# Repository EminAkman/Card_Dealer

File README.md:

# CDM (Kart Dağıtıcı Makine)

Bu repo, hem kendimi geliştirmek hem de geliştirme ve kullanım sürecinde keyif almak amacıyla tasarladığım otomatik kart dağıtma makinesinin (Card Dealing Machine - CDM) tasarım, yazılım ve donanım dosyalarını içerir.

## Proje Yapısı

- **[CAD_Files](CAD_Files/)**: Mekanik gövde ve parçalara ait 3B CAD tasarımları ve montaj dosyaları.
  - **[Upper_Parts](CAD_Files/Upper_Parts/)**: Kart haznesi, karıştırma ve itme mekanizması parçaları.
  - **[Middle_Parts](CAD_Files/Middle_Parts/)**: Kart fırlatma mekanizması ve OLED ekran montaj parçaları.
  - **[Lower_Parts](CAD_Files/Lower_Parts/)**: Taban gövdesi, motorlar, sensörler ve elektronik taşıyıcı parçaları.
- **[Code](Code/)**: Makinenin gömülü yazılımı ve kaynak kodları.
- **[PCB_Files](PCB_Files/)**: Elektronik devre kartı (PCB) tasarımları ve şematikler.

## Lisans

Bu proje [GPL-3.0](LICENSE) kapsamında lisanslanmıştır.

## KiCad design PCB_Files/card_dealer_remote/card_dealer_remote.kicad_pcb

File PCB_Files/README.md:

# PCB ve Elektronik Tasarımlar

Bu dizin, Kart Dağıtıcı Makine'nin (CDM) elektronik devre şemalarını, baskı devre kartı (PCB) tasarımlarını ve elektronik bileşen CAD modellerini içerir.

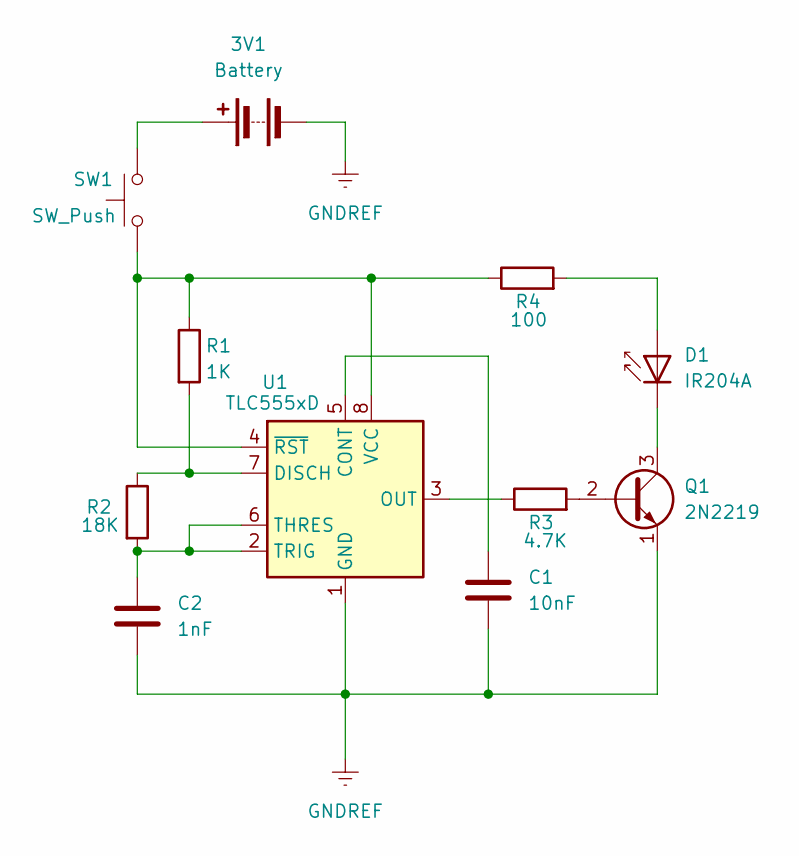
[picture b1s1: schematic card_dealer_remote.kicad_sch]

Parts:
3V1: Battery; BatteryHolder_MYOUNG_BS-07-A1BJ001_CR2032
C1: 10nF; CP_Radial_D5.0mm_P2.00mm
C2: 1nF; CP_Radial_D5.0mm_P2.00mm
D1: IR204A; LED_D3.0mm_IRBlack
Q1: 2N2219; TO-39-3
R1: 1K; R_Axial_DIN0207_L6.3mm_D2.5mm_P7.62mm_Horizontal
R2: 18K; R_Axial_DIN0207_L6.3mm_D2.5mm_P7.62mm_Horizontal
R3: 4.7K; R_Axial_DIN0207_L6.3mm_D2.5mm_P7.62mm_Horizontal
R4: 100; R_Axial_DIN0207_L6.3mm_D2.5mm_P7.62mm_Horizontal
SW1: SW_Push; SW_PUSH-12mm
U1: TLC555xD; DIP-8_W7.62mm

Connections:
GNDREF: 3V1.2 (-), C1.2, C2.2, Q1.1 (E), U1.1 (GND)
unnamed: 3V1.1 (+), SW1.2
unnamed: D1.2 (A), R4.2
unnamed: D1.1 (K), Q1.3 (C)
unnamed: Q1.2 (B), R3.2
unnamed: C1.1, U1.5 (CONT)
unnamed: R1.2, R2.1, U1.7 (DISCH)
unnamed: R3.1, U1.3 (OUT)
unnamed: C2.1, R2.2, U1.2 (TRIG), U1.6 (THRES)
unnamed: R1.1, R4.1, SW1.1, U1.4 (~RST), U1.8 (VCC)

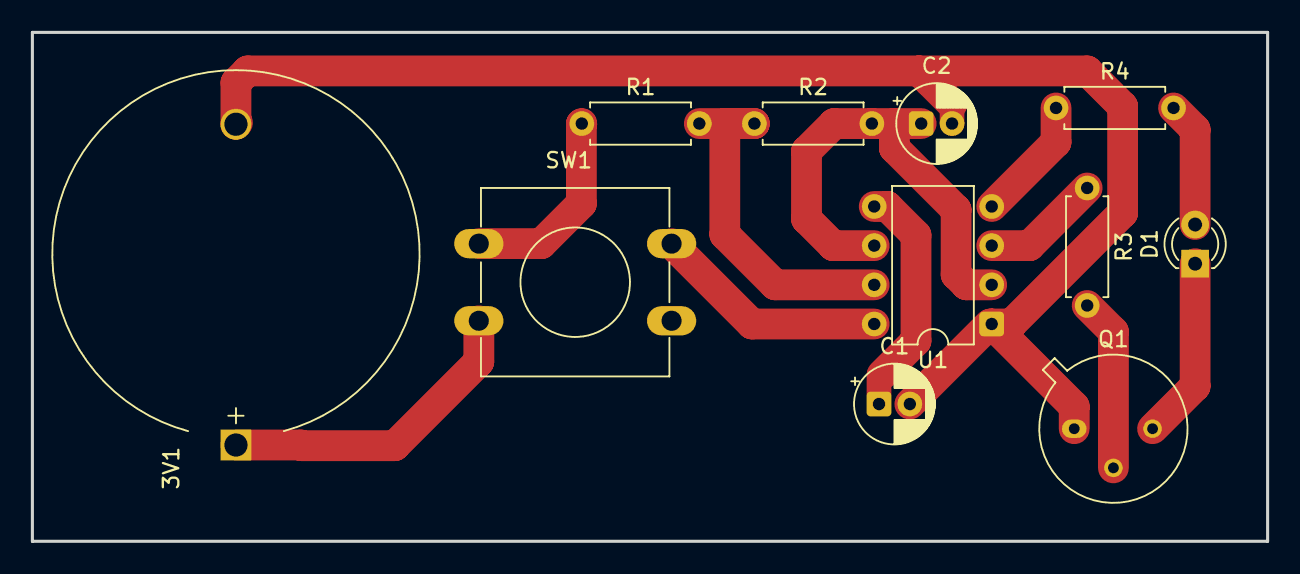
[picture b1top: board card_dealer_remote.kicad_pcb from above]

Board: 2 copper layers, 80.1 x 33.0 mm, 11 parts (0 on the bottom side), 10 nets.

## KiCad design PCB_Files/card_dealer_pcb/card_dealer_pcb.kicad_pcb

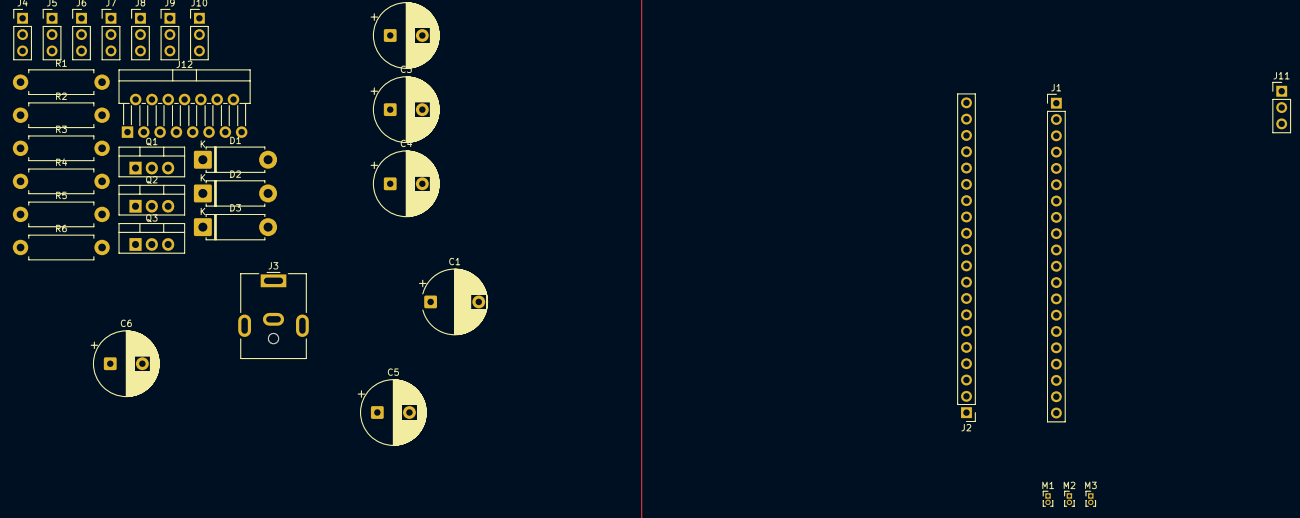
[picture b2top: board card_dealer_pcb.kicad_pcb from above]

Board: 2 copper layers, 33 parts (0 on the bottom side), 17 nets, no tracks yet.

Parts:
C1: 2200uf; CP_Radial_D10.0mm_P7.50mm
C2, C3, C4: 470uF; CP_Radial_D10.0mm_P5.00mm
C5, C6: 10uf; CP_Radial_D10.0mm_P5.00mm
D1, D2, D3: D; D_5W_P10.16mm_Horizontal
J1, J2: Conn_01x20_Pin; PinHeader_1x20_P2.54mm_Vertical
J3: Barrel_Jack; BarrelJack_CUI_PJ-063AH_Horizontal
J4: IR_Sensor_1; PinHeader_1x03_P2.54mm_Vertical
J5: IR_Sensor_2; PinHeader_1x03_P2.54mm_Vertical
J6: IR_Sensor_4; PinHeader_1x03_P2.54mm_Vertical
J7: IR_Sensor_5; PinHeader_1x03_P2.54mm_Vertical
J8: IR_Sensor_3; PinHeader_1x03_P2.54mm_Vertical
J9: IR_Sensor_6; PinHeader_1x03_P2.54mm_Vertical
J10: IR_Sensor_8; PinHeader_1x03_P2.54mm_Vertical
J11: IR_Sensor_7; PinHeader_1x03_P2.54mm_Vertical
J12: L298N; TO-220-15_P2.54x5.08mm_StaggerOdd_Lead4.58mm_Vertical
M1, M2, M3: Motor_DC; PinHeader_1x02_P1.00mm_Vertical
Q1, Q2, Q3: IRLZ44N; TO-220-3_Vertical
R1, R4, R6: 10K; R_Axial_DIN0411_L9.9mm_D3.6mm_P12.70mm_Horizontal
R2, R3, R5: 100; R_Axial_DIN0411_L9.9mm_D3.6mm_P12.70mm_Horizontal

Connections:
/3V3: J1.1, J2.3
/5V: C1.1, C2.2, C3.2, C4.2, C5.1, C6.1, D1.1 (K), D2.1 (K), D3.1 (K), J1.3, J2.1, J3.1, J4.3, J5.3, J6.3, J7.3, J8.3, J9.3, J10.3, J11.3, M1.1 (+), M2.1 (+), M3.1 (+), Q1.1 (G), Q2.1 (G), Q3.1 (G), R1.1, R2.2, R3.2, R4.1, R5.2, R6.1
/PA0: J2.15, R2.1
/PA1: J2.14, R3.1
/PA2: J2.13, R5.1
/PB3: J1.10, J4.1
/PB4: J1.9, J5.1
/PB5: J1.8, J8.1
/PB6: J1.7, J6.1
/PB7: J1.6, J7.1
/PB8: J1.5, J9.1
/PB9: J1.4, J11.1
/PB10: J2.4, J10.1
GND: C1.2, C2.1, C3.1, C4.1, C5.2, C6.2, J1.2, J2.2, J3.2, J4.2, J5.2, J6.2, J7.2, J8.2, J9.2, J10.2, J11.2, Q1.3 (S), Q2.3 (S), Q3.3 (S), R1.2, R4.2, R6.2
unnamed: D1.2 (A), M1.2 (-), Q1.2 (D)
unnamed: D2.2 (A), M2.2 (-), Q2.2 (D)
unnamed: D3.2 (A), M3.2 (-), Q3.2 (D)
